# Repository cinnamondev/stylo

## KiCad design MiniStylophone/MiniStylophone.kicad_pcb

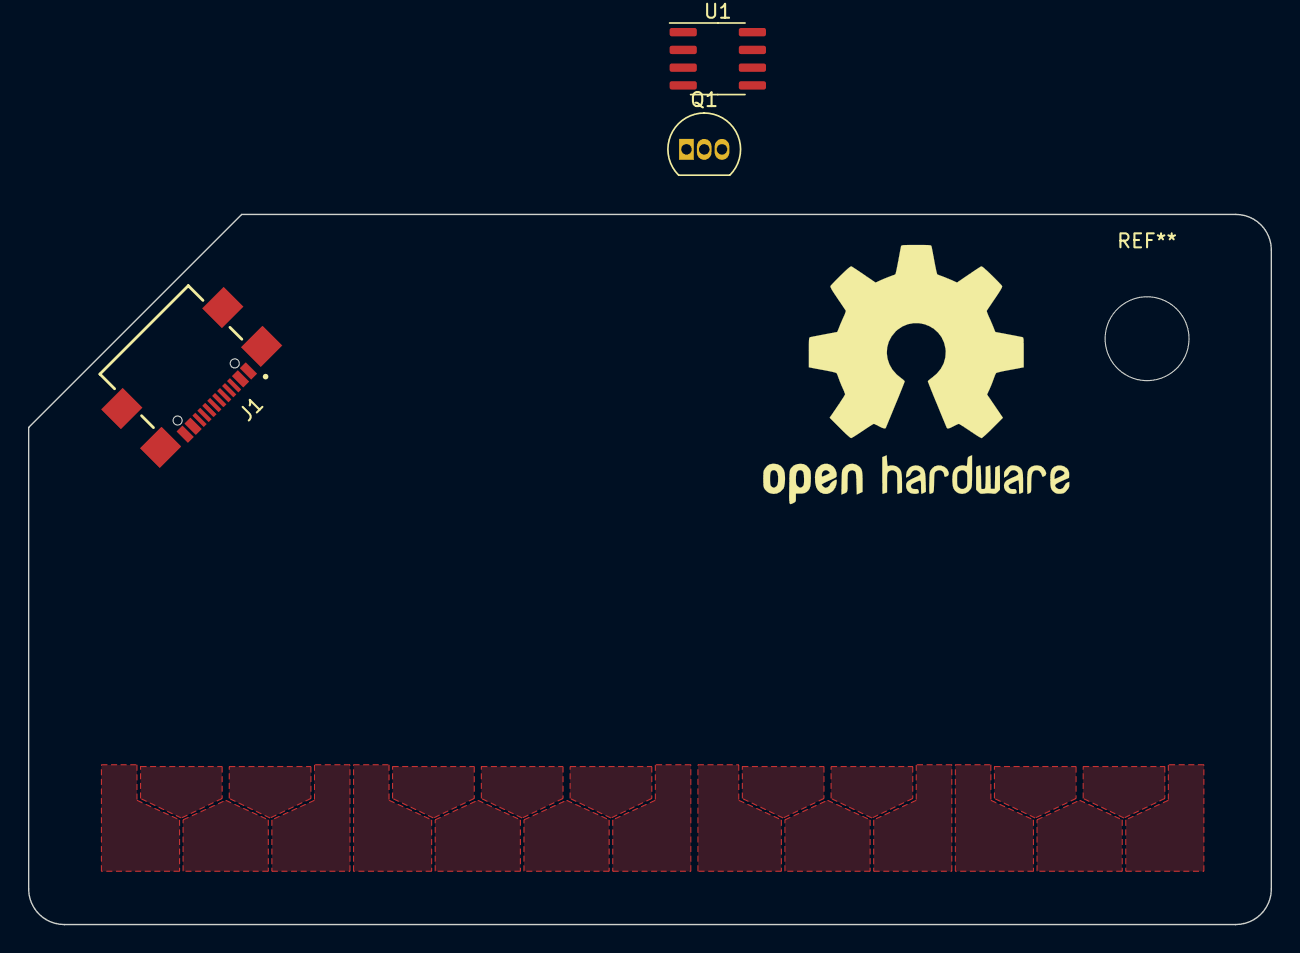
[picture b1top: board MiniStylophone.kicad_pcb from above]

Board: 2 copper layers, 88.9 x 50.8 mm, 3 parts (0 on the bottom side), 2 nets, no tracks yet.

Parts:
J1: USB_C_Receptacle_USB2.0; GCT_USB4110-GF-A_REVB
Q1: 2N3904; TO-92_Inline
U1: NE555D; SOIC-8_3.9x4.9mm_P1.27mm

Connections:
/V+: U1.4 (R), U1.8 (VCC)
GND: Q1.1 (E), U1.1 (GND)

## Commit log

2022-04-18 a bunch of stuff
    wooo
